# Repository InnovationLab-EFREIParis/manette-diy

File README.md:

# Manette DIY

Une super manette homemade basée sur un Raspberry Pi Pico

Le projet KiCAD est disponible dans le dossier `pcb/`

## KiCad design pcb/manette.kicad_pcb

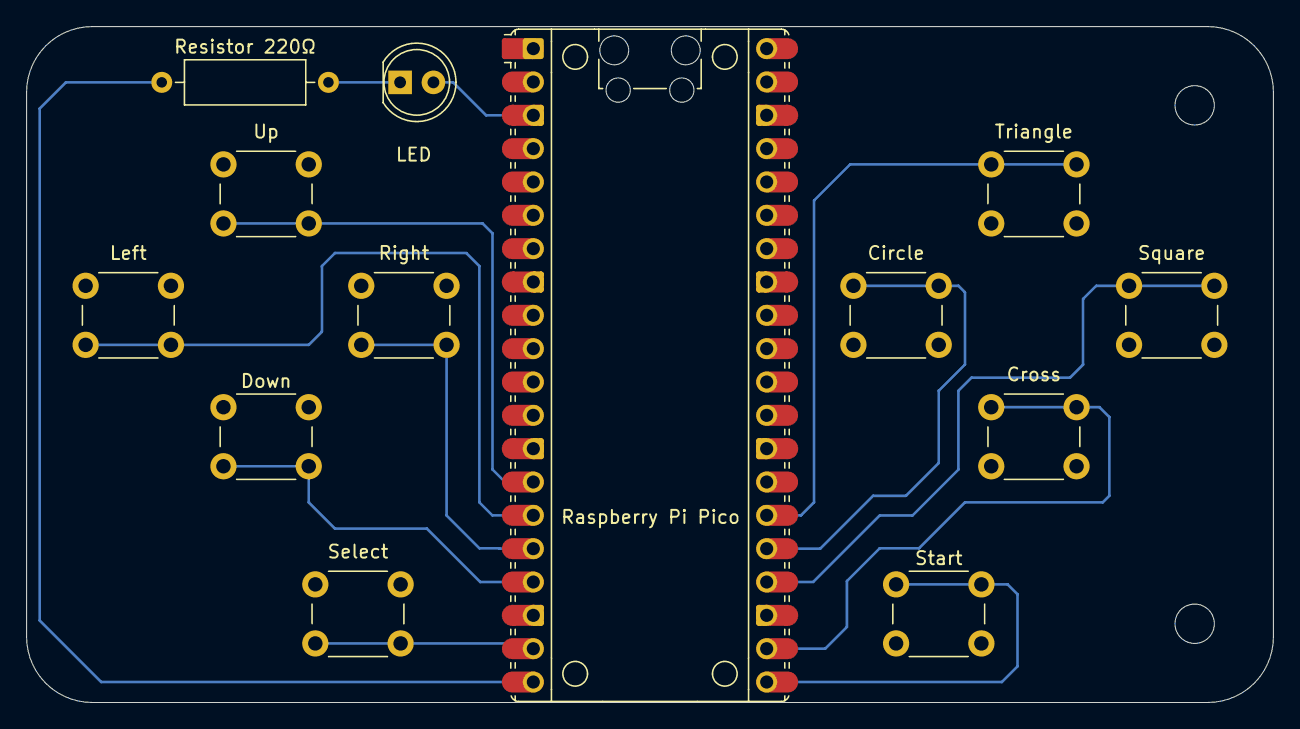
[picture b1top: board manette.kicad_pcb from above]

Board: 2 copper layers, 95.0 x 51.5 mm, 13 parts (0 on the bottom side), 13 nets.

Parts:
Circle: Circle; SW_PUSH_6mm_H4.3mm
Cross: Cross; SW_PUSH_6mm_H4.3mm
Down: Down; SW_PUSH_6mm_H4.3mm
LED: Blue; LED_D5.0mm
Left: Left; SW_PUSH_6mm_H4.3mm
Raspberry Pi Pico: RaspberryPi_Pico; RaspberryPi_Pico_Common
Resistor 220Ω: 220Ω; R_Axial_DIN0309_L9.0mm_D3.2mm_P12.70mm_Horizontal
Right: Right; SW_PUSH_6mm_H4.3mm
Select: Select; SW_PUSH_6mm_H4.3mm
Square: Square; SW_PUSH_6mm_H4.3mm
Start: Start; SW_PUSH_6mm_H4.3mm
Triangle: Triangle; SW_PUSH_6mm_H4.3mm
Up: Up; SW_PUSH_6mm_H4.3mm

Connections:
GND: Circle.2, Cross.2, Down.1, LED.2 (A), Left.1, Raspberry Pi Pico.3 (GND), Raspberry Pi Pico.8 (GND), Raspberry Pi Pico.13 (GND), Raspberry Pi Pico.18 (GND), Raspberry Pi Pico.23 (GND), Raspberry Pi Pico.28 (GND), Raspberry Pi Pico.38 (GND), Right.1, Select.1, Square.2, Start.2, Triangle.2, Up.1
unnamed: Raspberry Pi Pico.14 (GPIO10), Up.2
unnamed: Left.2, Raspberry Pi Pico.15 (GPIO11)
unnamed: Raspberry Pi Pico.16 (GPIO12), Right.2
unnamed: Down.2, Raspberry Pi Pico.17 (GPIO13)
unnamed: Raspberry Pi Pico.19 (GPIO14), Select.2
unnamed: Raspberry Pi Pico.20 (GPIO15), Resistor 220Ω.1
unnamed: Raspberry Pi Pico.21 (GPIO16), Start.1
unnamed: Cross.1, Raspberry Pi Pico.22 (GPIO17)
unnamed: Raspberry Pi Pico.24 (GPIO18), Square.1
unnamed: Circle.1, Raspberry Pi Pico.25 (GPIO19)
unnamed: Raspberry Pi Pico.26 (GPIO20), Triangle.1
unnamed: LED.1 (K), Resistor 220Ω.2

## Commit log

2025-03-07 initialize repository
2025-03-07 switched tracks
2025-03-10 small routing fix for more grounding
2025-03-10 adjusted report by removing joysticks
2025-03-10 Update LICENSE to GNU GPL v3
2025-03-10 added readme and removed kicad outputs
2025-03-14 updated code for the pico core
2025-03-17 updated PCB for smaller controllers
2025-03-17 ajout trous de fixation, élargissement des pistes et des pads
2025-03-18 replaced edge.cut holes with footprint drill holes
2025-03-18 fixed design constraints and rolled back to edge.cut holes
2025-03-19 changed language to micropython
2025-03-19 added working LED (with PWM)
2025-03-20 Update code.py for the LED
2025-03-20 enabled usb drive
2025-03-20 Add img folder
